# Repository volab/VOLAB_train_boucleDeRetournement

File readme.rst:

=======================================================
Informations générales VOLAB_train_boucleDeRetournement
=======================================================

:Auteur:            `MajorLee95 <https://github.com/MajorLee95>`_
:Projet:             VOLAB_train_boucleDeRetournement
:dépôt GitHub:       https://github.com/volab/VOLAB_train_boucleDeRetournement
:documentation:      http://www.vorobotics.com/wiki/index.php?title=Boucle_de_retournement   
:Licence:            CC0
:Liens:              https://creativecommons.org/licenses

Description
===========

 Le réseau de train électrique miniature du VoLAB comporte une boucle.
 
 Il s'agit ici de traiter le court-circuit qui se produit au passage de cette boucle.

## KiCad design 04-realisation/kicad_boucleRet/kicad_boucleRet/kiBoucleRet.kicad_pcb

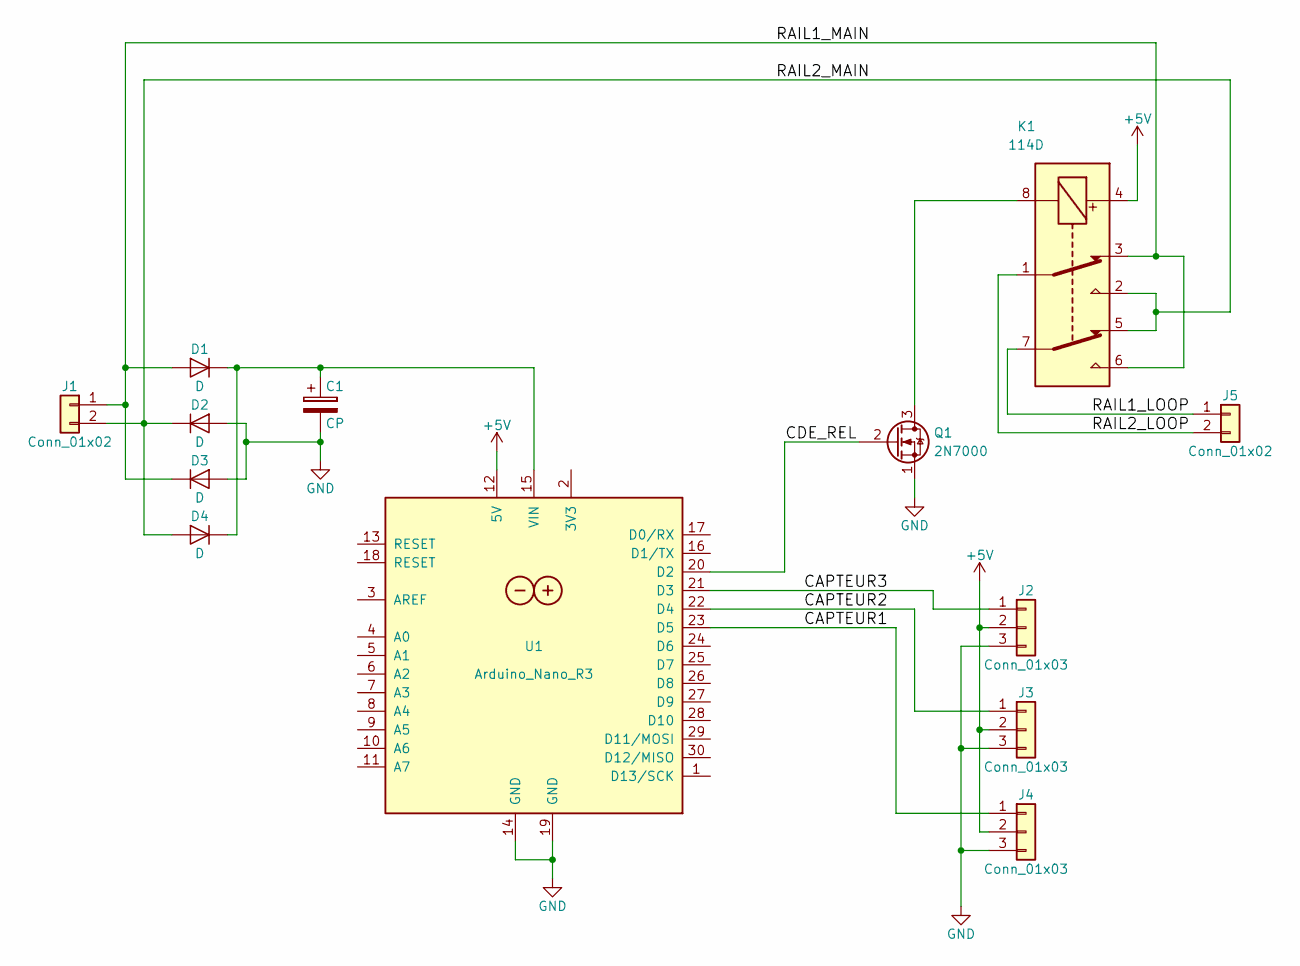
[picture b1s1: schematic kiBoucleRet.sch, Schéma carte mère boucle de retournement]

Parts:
C1: CP; CP_Radial_D5.0mm_P2.50mm
D1, D3: D; 1N4004_P15.24mm_Horizontal
D2, D4: D; D_T-1_P10.16mm_Horizontal
J1, J5: Conn_01x02; bornier2
J2, J3, J4: Conn_01x03; SL-103-X-XX_1x03
K1: 114D; R114D_ronde
Q1: 2N7000; TO-92_Inline_Narrow_Oval
U1: Arduino_Nano_R3; Arduino_Nano

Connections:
+5V: J2.2, J3.2, J4.2, K1.4, U1.12 (5V)
/CAPTEUR1: J4.1, U1.23 (D5)
/CAPTEUR2: J3.1, U1.22 (D4)
/CAPTEUR3: J2.1, U1.21 (D3)
/CDE_REL: Q1.2 (G), U1.20 (D2)
/RAIL1_LOOP: J5.1, K1.7
/RAIL1_MAIN: D1.2 (A), D3.1 (K), J1.1, K1.3, K1.6
/RAIL2_LOOP: J5.2, K1.1
/RAIL2_MAIN: D2.1 (K), D4.2 (A), J1.2, K1.2, K1.5
GND: C1.2, D2.2 (A), D3.2 (A), J2.3, J3.3, J4.3, Q1.1 (S), U1.14 (GND), U1.19 (GND)
unnamed: C1.1, D1.1 (K), D4.1 (K), U1.15 (VIN)
unnamed: K1.8, Q1.3 (D)

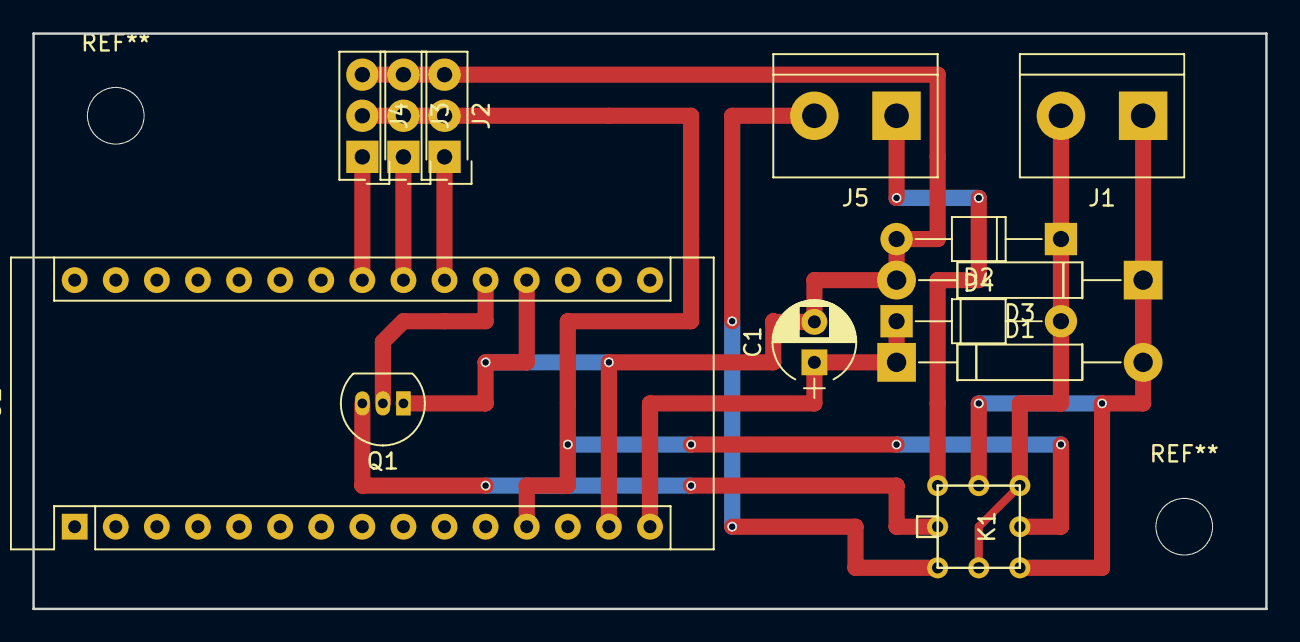
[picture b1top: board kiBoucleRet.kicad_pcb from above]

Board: 4 copper layers, 76.2 x 35.6 mm, 13 parts (0 on the bottom side), 12 nets.

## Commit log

2018-10-06 Creation readme.rst + passage doc conception en CC0
2018-10-06 ajout kicad submodule
2018-10-06 deuxième tentative d'ajout de 04-realisation/kicad_boucleRet dans le dépot distant
2018-10-06 troisieme tentative ajout kicad projet
2018-10-06 suppression 2 images dépot distant
2018-10-06 Ajout des fichiers CAO
2018-10-06 ajout du pdf de l'article du wiki
